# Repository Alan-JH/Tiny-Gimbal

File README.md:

# Tiny-Gimbal
Code and pcb for two axis self stabilizing servo gimbal using BNO055 and ATTiny16x4 for TJUAV

### V1 
Version for the See3Cam CU135, with 3 axis stabilization. Code was developed and used, but PCB was never manufactured

### V2.1
Due to poor results with the See3Cam, TJUAV has decided to switch to the Sony alpha cameras, specifically the A5100. However, all testing so far has been done with an A5000 camera we already have, which should be dimensionally identical to the A5100, although slower.

Yaw stabilization was removed, for the sake of weight saving and ease of cable management
The mechanism for the gimbal was completely overhauled, needing to be stronger for the camera being 400g instead of 20g
The gimbal was designed for the camera to be easily removeable this time around
A kill switch, and two control buttons (one for centering all servos, and one for putting the gimbal in a position where the camera is easily removeable) were added

Tested and working

### V2.2
Small feature improvements, including:
Zip tie points on the camera mount
Consolidating UART debug connectivity into the UPDI header using a SPDT DIP switch
LED indicators to tell whether the gimbal is centered, in remove position, and powered
U mount X frame instead of an L bracket, to support the camera from both sides and minimize lateral load on the X servo
Single bearing instead of dual bearing Y frame mechanism, to save mass
Sideways X servo, to save mass and size
Integrated buck converter mount on the spar clamp

Tested and working

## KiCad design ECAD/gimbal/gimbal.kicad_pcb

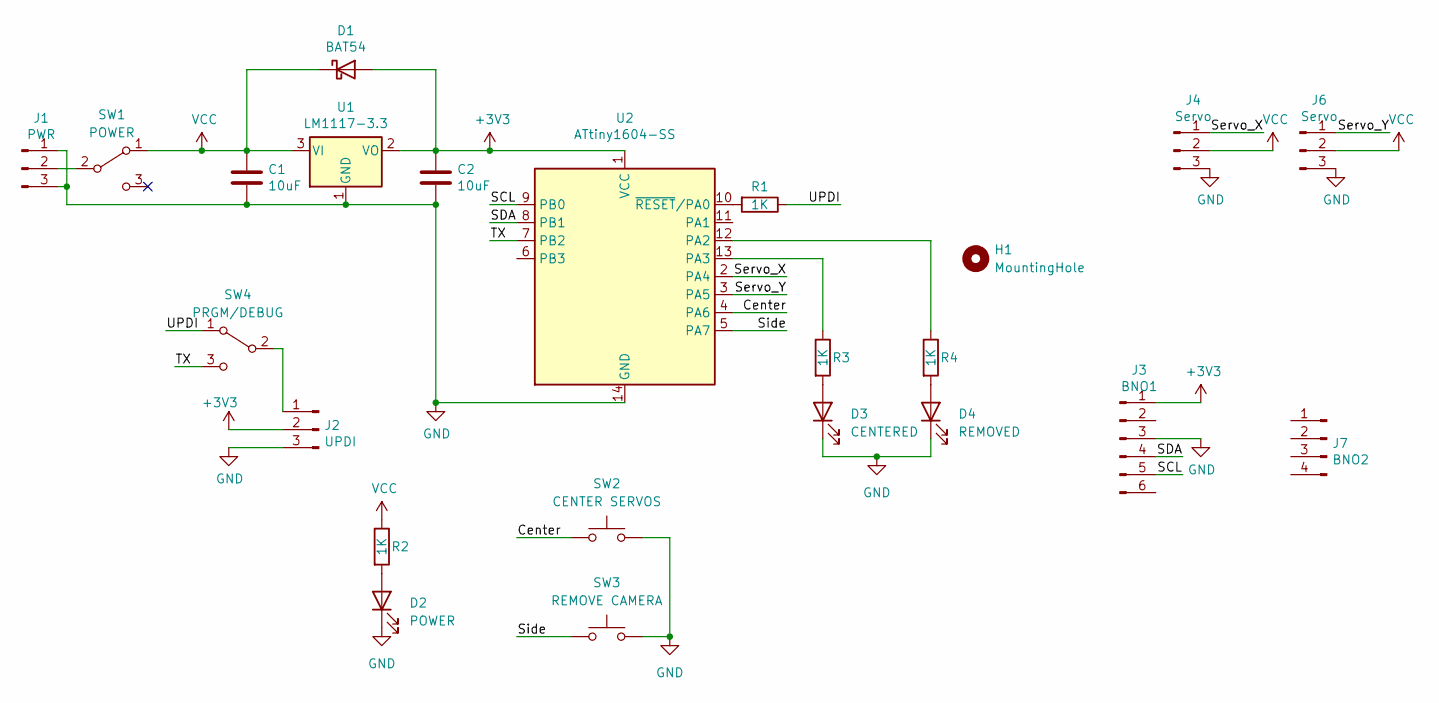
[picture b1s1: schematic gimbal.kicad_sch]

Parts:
C1, C2: 10uF; C_0805_2012Metric
D1: BAT54; D_SOD-123
D2: POWER; D_0805_2012Metric
D3: CENTERED; D_0805_2012Metric
D4: REMOVED; D_0805_2012Metric
H1: MountingHole; MountingHole_3.2mm_M3
J1: PWR; PinHeader_1x03_P2.54mm_Vertical
J2: UPDI; PinHeader_1x03_P2.54mm_Vertical
J3: BNO1; PinHeader_1x06_P2.54mm_Vertical
J4, J6: Servo; PinHeader_1x03_P2.54mm_Vertical
J7: BNO2; PinHeader_1x04_P2.54mm_Vertical
R1, R2, R3, R4: 1K; R_1206_3216Metric
SW1: POWER; Switch
SW2: CENTER SERVOS; SW_PUSH_6mm
SW3: REMOVE CAMERA; SW_PUSH_6mm
SW4: PRGM/DEBUG; SW_Slide_1P2T_CK_OS102011MS2Q
U1: LM1117-3.3; SOT-223-3_TabPin2
U2: ATtiny1604-SS; SOIC-14_3.9x8.7mm_P1.27mm

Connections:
+3V3: C2.1, D1.2 (A), J2.2, J3.1, U1.2 (VO), U2.1 (VCC)
/Center: SW2.1, U2.4 (PA6)
/SCL: J3.5, U2.9 (PB0)
/SDA: J3.4, U2.8 (PB1)
/Servo_X: J4.1, U2.2 (PA4)
/Servo_Y: J6.1, U2.3 (PA5)
/Side: SW3.1, U2.5 (PA7)
/TX: SW4.3 (C), U2.7 (PB2)
/UPDI: R1.1, SW4.1 (A)
GND: C1.2, C2.2, D2.1 (K), D3.1 (K), D4.1 (K), J1.1, J1.3, J2.3, J3.3, J4.3, J6.3, SW2.2, SW3.2, U1.1 (GND), U2.14 (GND)
unnamed: D2.2 (A), R2.2
unnamed: D3.2 (A), R3.2
unnamed: D4.2 (A), R4.2
unnamed: J1.2, SW1.2 (B)
unnamed: J2.1, SW4.2 (B)
unnamed: R1.2, U2.10 (~RESET/PA0)
unnamed: R3.1, U2.13 (PA3)
unnamed: R4.1, U2.12 (PA2)
VCC: C1.1, D1.1 (K), J4.2, J6.2, R2.1, SW1.1 (A), U1.3 (VI)

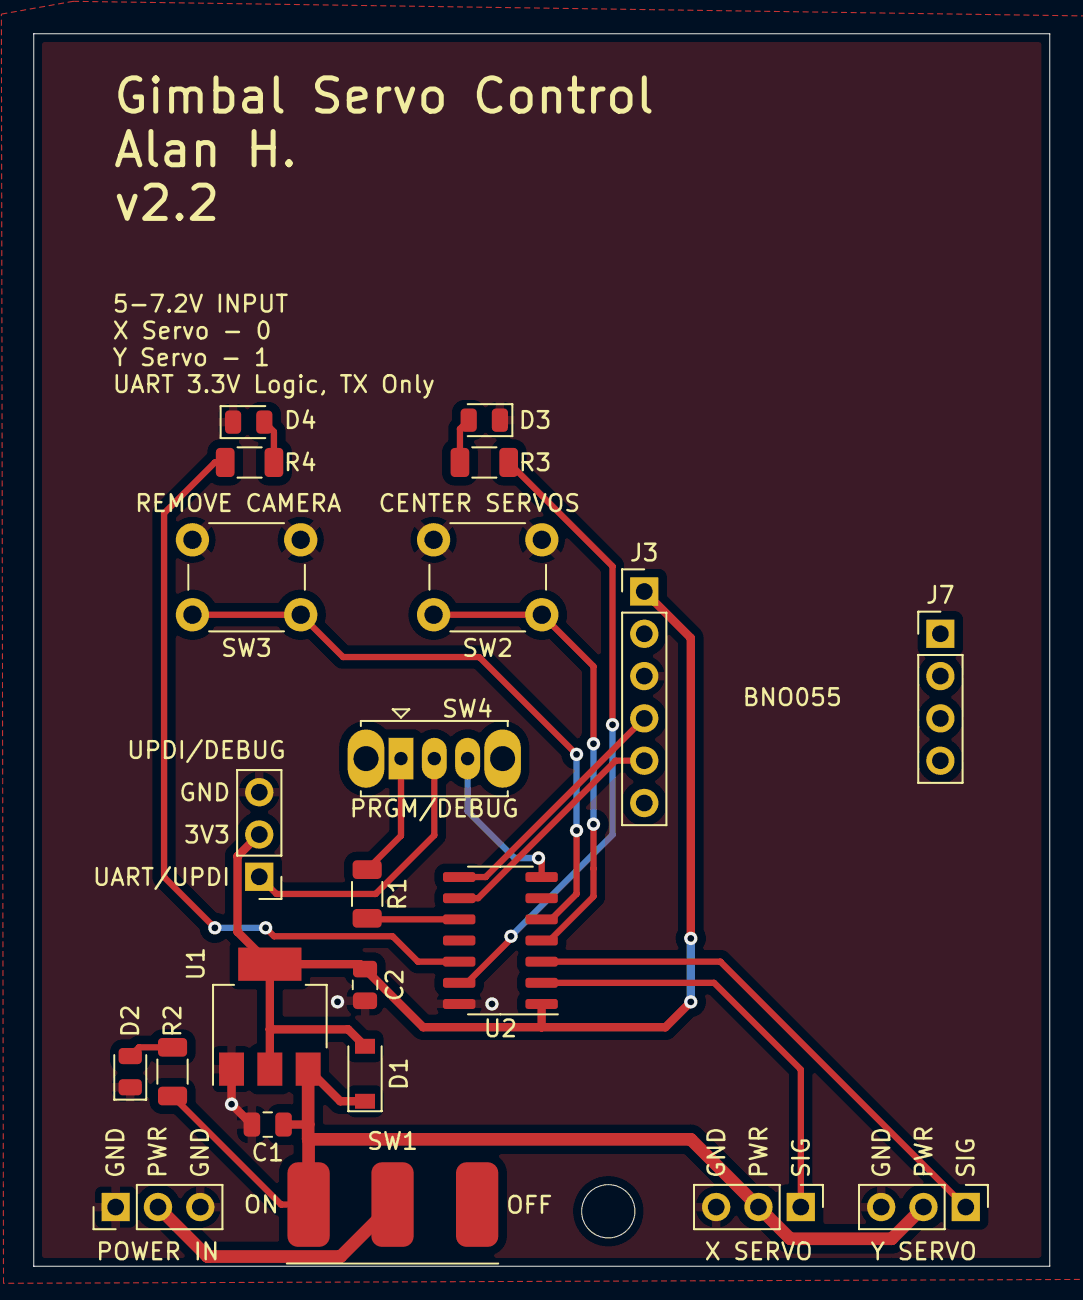
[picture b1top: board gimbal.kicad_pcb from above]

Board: 2 copper layers, 61.0 x 74.0 mm, 23 parts (0 on the bottom side), 19 nets.

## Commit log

2022-01-12 Init
2022-01-15 Ari's pid changes
2022-01-15 what is even happening
2022-01-16 "turn logic"
2022-01-16 Fix almost everything
2022-01-17 add duty cycle calc
2022-01-17 long long man
2022-01-18 notifthresh back to 5
2022-01-26 add pcb
2022-02-11 implement remap function
2022-02-12 quat attempt
2022-09-11 v2 for A5100 gimbal
2022-09-11 Add centering and remove buttons
2022-09-19 code changes
2022-09-20 Fix compile errors
2022-09-20 code tuning and sch changes for v2.2
2022-09-21 update footprints
2022-09-21 purge backups, gitignore
2022-09-22 v2.2 complete
2022-09-22 MCAD export
2022-09-27 PD implementation
2022-09-27 PD correction and debugging
2022-09-27 begin implementing integral
2022-09-27 finish integral implementation
2022-09-27 integral doesnt help anyways
2022-09-28 separate x and y tuning
2022-09-29 add center and remove LED functions for v2.2, comment code
2022-10-05 finish tuning, add delay for smoother operation
2022-10-10 Make PCB easier to remove
